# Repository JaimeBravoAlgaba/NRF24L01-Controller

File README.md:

# NRF24L01-Controller
RF controller, based on the NRF24L01 module.

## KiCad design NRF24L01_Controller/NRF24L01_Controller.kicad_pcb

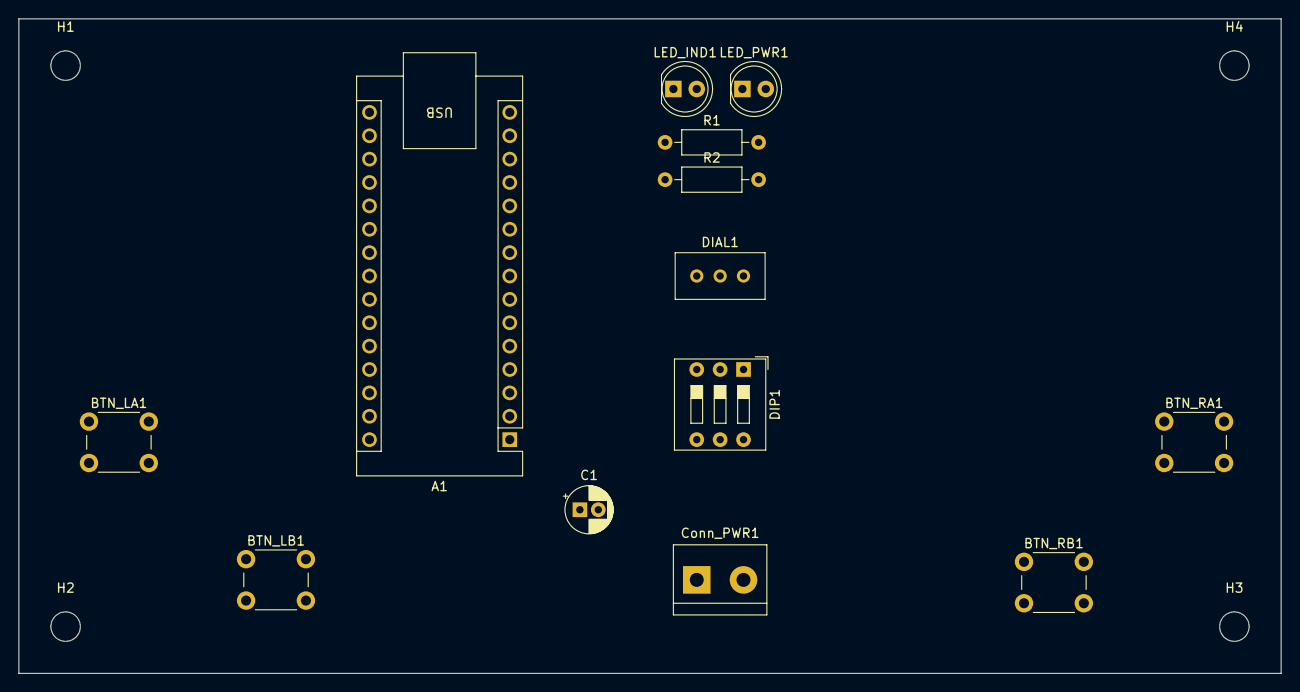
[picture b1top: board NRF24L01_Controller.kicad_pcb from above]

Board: 2 copper layers, 137.2 x 71.1 mm, 17 parts (0 on the bottom side), 6 nets, no tracks yet.

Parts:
A1: Arduino_Nano_Every; Arduino_Nano
BTN_LA1: SW_Push_Dual; SW_PUSH_6mm_H8mm
BTN_LB1: SW_Push_Dual; SW_PUSH_6mm_H8mm
BTN_RA1: SW_Push_Dual; SW_PUSH_6mm_H8mm
BTN_RB1: SW_Push_Dual; SW_PUSH_6mm_H8mm
C1: 1uF; CP_Radial_D5.0mm_P2.00mm
Conn_PWR1: Screw_Terminal_01x02; TerminalBlock_bornier-2_P5.08mm
DIAL1: R_Potentiometer; Potentiometer_Bourns_3296W_Vertical
DIP1: SW_DIP_x03; SW_DIP_SPSTx03_Slide_9.78x9.8mm_W7.62mm_P2.54mm
H1, H2, H3, H4: MountingHole; MountingHole_3.2mm_M3
LED_IND1: LED; LED_D5.0mm
LED_PWR1: LED; LED_D5.0mm
R1, R2: R; R_Axial_DIN0207_L6.3mm_D2.5mm_P10.16mm_Horizontal

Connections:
+3V3: A1.17 (3V3), C1.1
+5V: A1.27 (+5V), DIAL1.1
GND: A1.4 (GND), A1.29 (GND), BTN_LA1.2, BTN_LB1.2, BTN_RA1.2, BTN_RB1.2, C1.2, Conn_PWR1.2, DIAL1.3, DIP1.1, DIP1.2, DIP1.3, R1.2, R2.1
unnamed: LED_IND1.1 (K), R2.2
unnamed: LED_PWR1.1 (K), R1.1
VDC: A1.30 (VIN), LED_PWR1.2 (A)

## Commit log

2023-03-22 Schematic
